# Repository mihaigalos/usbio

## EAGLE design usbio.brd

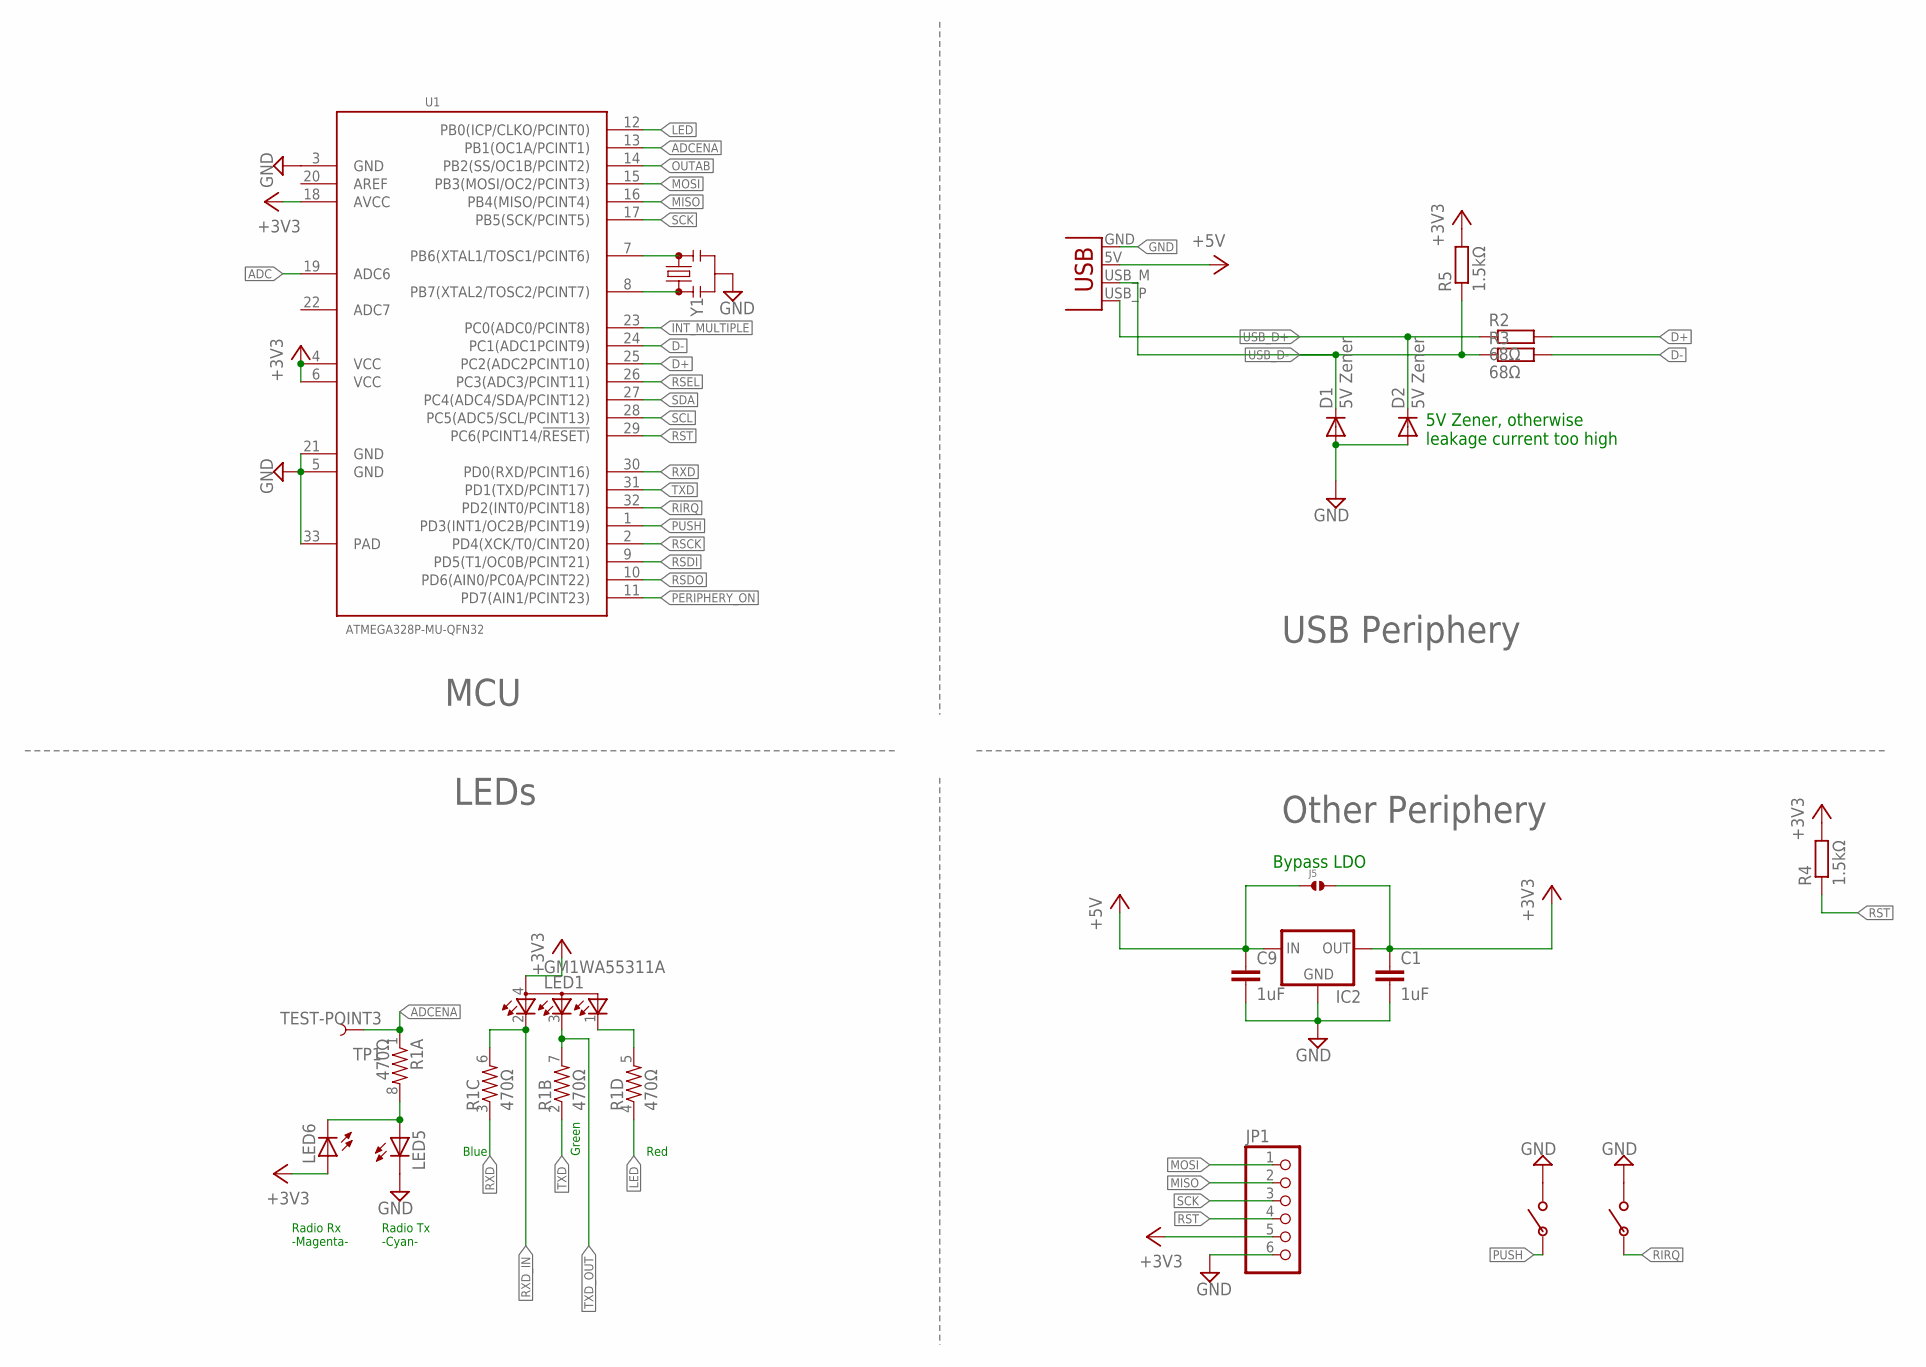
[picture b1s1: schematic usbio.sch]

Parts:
C1, C9: 1uF; C0603
D1, D2: 5V Zener; SOD523
IC2: MCP1700TT; SOT-23
J5: SOLDERJUMPER.2.MED; 2.MED
JP1: PINHD-1X6; 1X06
JP3: USBPCB; USB-A-PCB
LED1: GM1WA55311A
LED5, LED6: LED0603; LED-0603
R1: 470Ω; 0603-ARV
R2, R3: 68Ω; R0603
R4, R5: 1.5kΩ; R0603
TP1: TEST-POINT3; PAD.03X.03
U1: ATMEGA328P-MU-QFN32; QFN32G-0.5-5X5MM
U$2, U$3: PUSHBUTTON_4X2.5
Y1: RESONATORSMD-3.2X1.3; RESONATOR-SMD-3.2X1.3

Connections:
+3V3: C1.1, IC2.2 (OUT), J5.2, JP1.5, LED1.4 (A), LED6.A, R4.2, R5.2, U1.4 (VCC), U1.6 (VCC), U1.18 (AVCC)
+5V: C9.1, IC2.3 (IN), J5.1, JP3.5V (VBUS)
ADC: U1.19 (ADC6)
ADCENA: R1.1, TP1.P$1, U1.13 (PB1(OC1A/PCINT1))
D+: R2.2, U1.25 (PC2(ADC2PCINT10))
D-: R3.2, U1.24 (PC1(ADC1PCINT9))
GND: C1.2, C9.2, D1.A, D2.A, IC2.1 (GND), JP1.6, JP3.GND, LED5.C, U1.3 (GND), U1.5 (GND), U1.21 (GND), U1.33 (PAD), U$2.P$2, U$3.P$2, Y1.2
INT_MULTIPLE: U1.23 (PC0(ADC0/PCINT8))
LED: R1.4 (1), U1.12 (PB0(ICP/CLKO/PCINT0))
MISO: JP1.2, U1.16 (PB4(MISO/PCINT4))
MOSI: JP1.1, U1.15 (PB3(MOSI/OC2/PCINT3))
unnamed: U1.7 (PB6(XTAL1/TOSC1/PCINT6)), Y1.3
unnamed: U1.8 (PB7(XTAL2/TOSC2/PCINT7)), Y1.1
unnamed: LED5.A, LED6.C, R1.8 (2)
unnamed: LED1.1 (CGREEN), R1.5 (2)
OUTAB: U1.14 (PB2(SS/OC1B/PCINT2))
PERIPHERY_ON: U1.11 (PD7(AIN1/PCINT23))
PUSH: U1.1 (PD3(INT1/OC2B/PCINT19)), U$3.P$1
RIRQ: U1.32 (PD2(INT0/PCINT18)), U$2.P$1
RSCK: U1.2 (PD4(XCK/T0/CINT20))
RSDI: U1.9 (PD5(T1/OC0B/PCINT21))
RSDO: U1.10 (PD6(AIN0/PC0A/PCINT22))
RSEL: U1.26 (PC3(ADC3/PCINT11))
RST: JP1.4, R4.1, U1.29 (PC6(PCINT14/!RESET))
RXD: R1.3 (1), U1.30 (PD0(RXD/PCINT16))
RXD_IN: LED1.2 (CRED), R1.6 (2)
SCK: JP1.3, U1.17 (PB5(SCK/PCINT5))
SCL: U1.28 (PC5(ADC5/SCL/PCINT13))
SDA: U1.27 (PC4(ADC4/SDA/PCINT12))
TXD: R1.2 (1), U1.31 (PD1(TXD/PCINT17))
TXD_OUT: LED1.3 (CBLUE), R1.7 (2)
USB_D+: D2.C, JP3.USB_P (D+), R2.1
USB_D-: D1.C, JP3.USB_M (D-), R3.1, R5.1

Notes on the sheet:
Blue
Green
Red
Radio Rx -Magenta-
Radio Tx -Cyan-
5V Zener, otherwise leakage current too high
USB Periphery
MCU
Other Periphery
LEDs
Bypass LDO

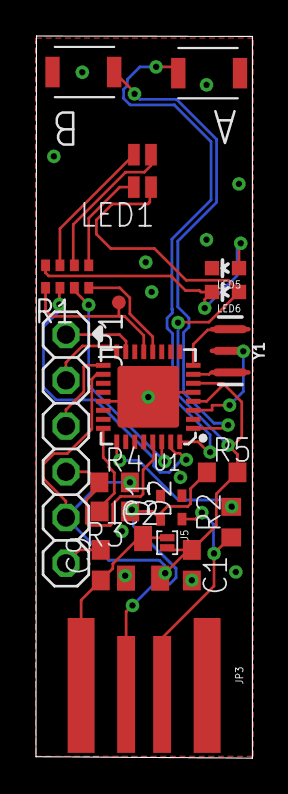
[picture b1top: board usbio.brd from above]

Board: 2 copper layers, 12.0 x 40.1 mm, 21 parts (0 on the bottom side), 23 nets.

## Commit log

2019-11-13 Initial commit, routed
2019-11-14 Adjust tStop and bStop for window
2019-11-14 Add QR and name
2019-11-14 Extend soldermask
2019-11-14 Correct routing to led
2019-11-15 Route missing signals, fix warnings
2019-11-15 Add AB labels to buttons
2019-11-16 Straighten pins
2019-11-16 Soldermask traces around rgb
2019-11-16 Comartiment schematic
2019-11-16 No mask rgb bottom
2019-11-16 Add MOSI indicator
2019-11-16 Rearrange vias around array
2019-11-16 Add LDO bypass jumper
2019-11-16 Remove GND via too close to 5V
2019-11-16 Add dimmensions
2019-11-16 Narrow sides to fit usb 12mm width constraint
2019-11-16 Optimize vias
2019-11-16 Add width docu
2019-11-16 Add pullup on RST

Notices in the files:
parts and their libraries:
SparkFun: Licensing: CC v3.0 Share-Alike You are welcome to use this library for commercial purposes.
SparkFun-Clocks: Licensing: Creative Commons ShareAlike 4.0 International - https://creativecommons.org/licenses/by-sa/4.0
